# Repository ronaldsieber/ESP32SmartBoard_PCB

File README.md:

# ESP32SmartBoard_PCB
**KiCad project of a Printed Cuircit Board (PCB) for ESP32 with Temperature/Humidity/CO2 Sensors, User LEDs and Buttons.**

In the past I've implemented various Smart Projects with the ESP32 on break-out boards. On the one hand, break-out boards are very useful because they make hardware modifications as easy as software changes. On the other hand, it is very cumbersome to build several copies of the same circuit with break-out boards. Furthermore, they are mechanically fragile and not really particularly visually appealing. Therefore they are not very suitable for permanent use in the visible area of living rooms.

For this reason I designed the **ESP32SmartBoard_PCB**, which combines different projects on a single, professionally producible PCB. This allows now for reproducing multiple copies of a device without great effort and hide them in a small housing if necessary.

## Board Features

The *ESP32SmartBoard_PCB* contains the following components:
- ESP32 Development Kit
- DHT22 (combined temperature and humidity sensor)
- MH-Z19 (CO2 sensor with integrated temperature sensor)
- 9 freely usable user LEDs (LED0..LED8, arranged in one row and usable as a LED Bar)
- 3 freely usable user Buttons (KEY0, KEY1, BLE_CFG)

![\[kicad_3d_model\]](Documentation/ESP32SmartBoard_PCB.3d-model.png)

## Board Description

The *ESP32SmartBoard_PCB* is a two-layer Printed Circuit Board (PCB), assembled on one side and only uses THT components (Through Hole Technology) that are very easy to solder. It can therefore be used very easily also by students and hobbyists.

The values of all components are specified in the [Schematic](Documentation/ESP32SmartBoard_PCB.sch.pdf).

The PCB size and the positions of the mounting holes allow installation in the plastic universal housing of 135 x 95 x 45 mm (article number 523117). This polystyrene housing (EPS) can be easily processed mechanically (e.g. cut out a viewing window for the LED Bar). It is available from various providers on the Internet.

![\[ESP32SmartBoard_OpenFrame_with_Box\]](Documentation/ESP32SmartBoard_OpenFrame_with_Box.jpg)

By searching in the Internet, several PCB manufacturers can be found who are able to directly import the KiCad layout file [ESP32SmartBoard_PCB.kicad_pcb](ESP32SmartBoard_PCB/ESP32SmartBoard_PCB.kicad_pcb). The PCBs with silkscreen (assembly printing) on the top are then sent by post after a few days.

## Power Supply

There are following options for the power supply of the board:
- Via USB connection of the ESP32 Development Kit (in this case Pin15/Vin of the ESP32DevKit acts as an output and supplies the rest of the circuit)
- Supply of 5 ... 6VDC to connector J1 (in this case the rest of the board supplies the ESP32DevKit and Pin15/Vin acts as an input)

## Commissioning

With the Arduino sketch from the [ESP32SmartBoard_IoCheck](https://github.com/ronaldsieber/ESP32SmartBoard_IoCheck) repository, all components of the board can be checked for correct function after assembly. The sketch is also a good starting point for new software projects based on this board.

## Schematic Symbols, Footprints and 3D Models

Not all schematic symbols, footprints and 3D models required for *ESP32SmartBoard_PCB* are contained in the native installed KiCad library. [External_KiCad_Parts.txt](Documentation/External_KiCad_Parts.txt) lists the additional components and their download links.

## Practice Notes

- The user LEDs are arranged in one row and can be used as a LED Bar. The colors of the LEDs should be selected according to the respective application. For example, to show the CO2 level in the form of a scale, the following grouping is suitable:
  * LED0..LED2: green = excellent
  * LED3..LED5: yellow = acceptable
  * LED6..LED8: red = critical

- It seems that there are several versions of the ESP32 Development Kit and the MH-Z19 CO2 sensor with pins of different widths. In my components, the diameter of the connection pins are larger than the diameter of the soldering pads in the footprint. This prevented me from soldering the components directly onto the board. However, I was able to solve the problem by using Pin Headers (see image above). The solder connections of the Pin Headers are small enough for the solder pads and the ESP32 Development Kit and MH-Z19 CO2 sensor can be easily plugged in.

## Software Projects for the ESP32SmartBoard

 - [ESP32SmartBoard_IoCheck](https://github.com/ronaldsieber/ESP32SmartBoard_IoCheck) - Checking of all components during commissioning and starting point for new software projects based on this board.
   
 - [ESP32SmartBoard_HttpSensors](https://github.com/ronaldsieber/ESP32SmartBoard_HttpSensors) - Embedded WebServer based Arduino Sketch for ESP32SmartBoard
   
 - [ESP32SmartBoard_MqttSensors](https://github.com/ronaldsieber/ESP32SmartBoard_MqttSensors) - MQTT Client based Arduino Sketch for ESP32SmartBoard

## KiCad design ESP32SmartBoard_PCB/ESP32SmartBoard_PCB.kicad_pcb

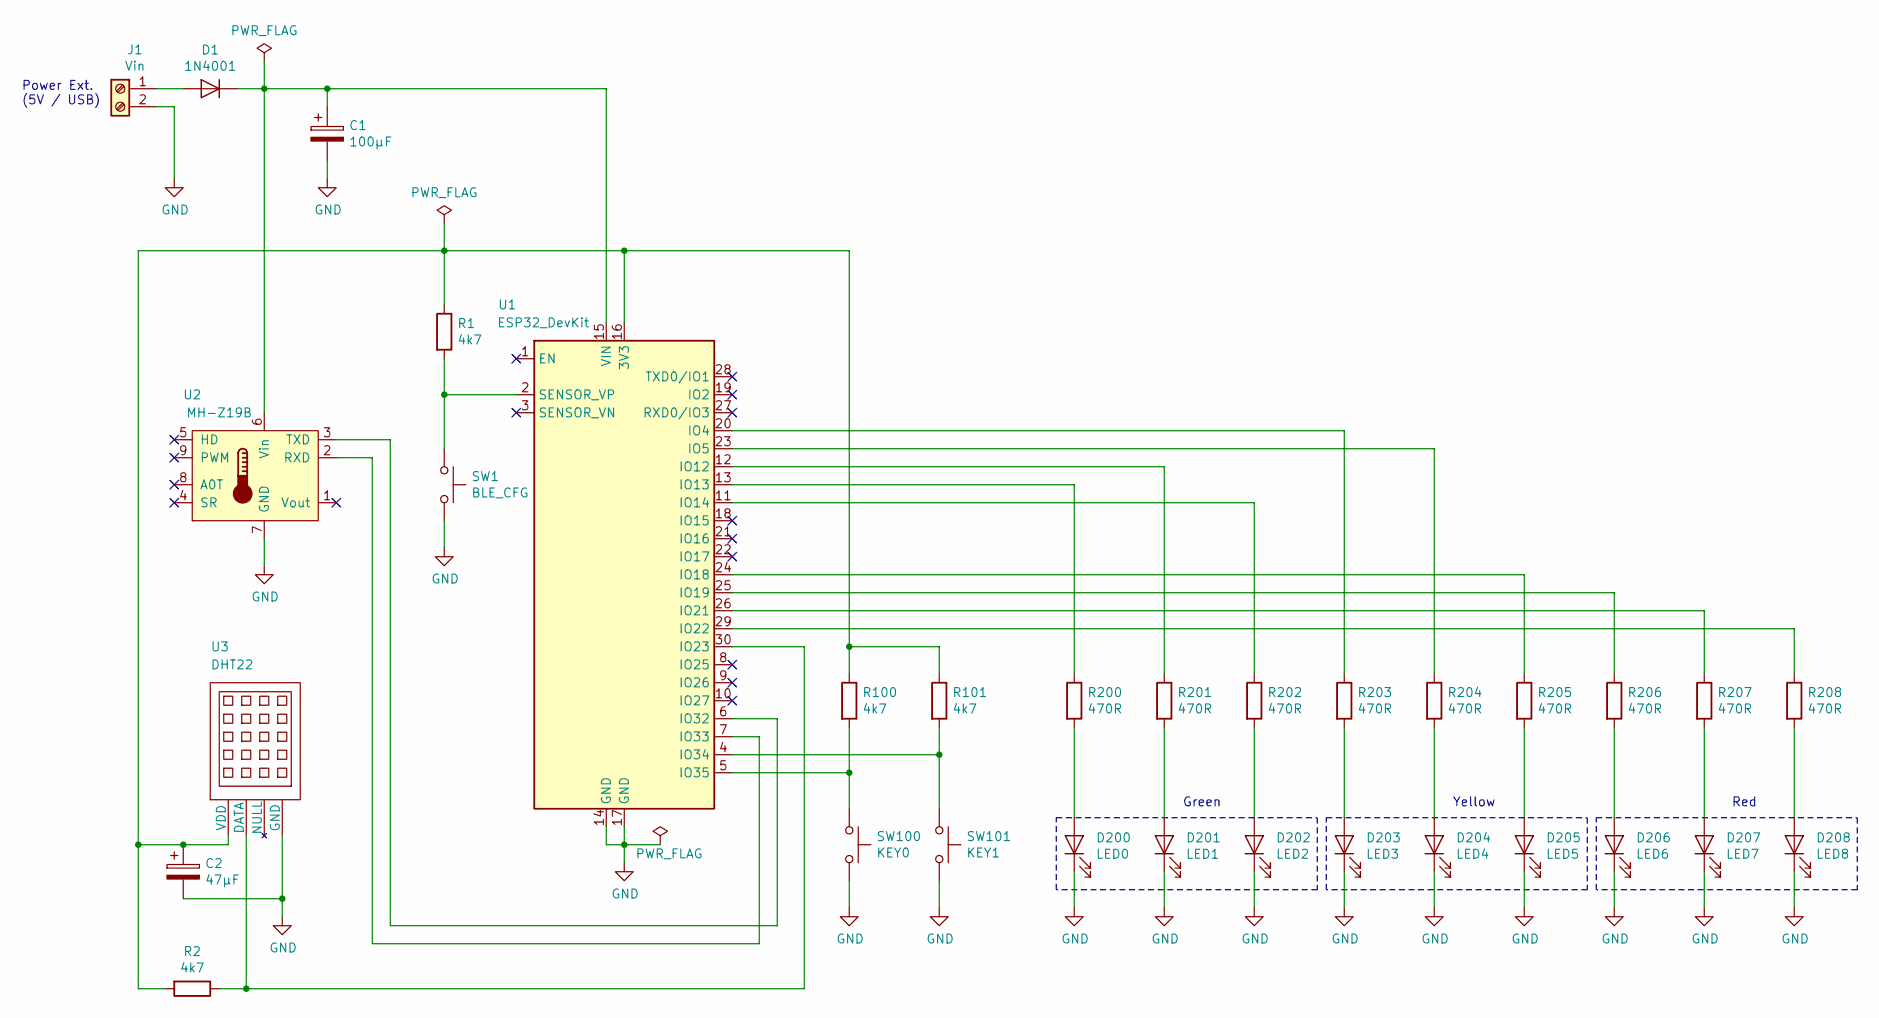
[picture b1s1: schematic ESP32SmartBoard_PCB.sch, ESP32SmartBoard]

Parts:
C1: 100µF; CP_Radial_D8.0mm_P3.50mm
C2: 47µF; CP_Radial_D8.0mm_P3.50mm
D1: 1N4001; D_5W_P12.70mm_Horizontal
D200: LED0; LED_D3.0mm
D201: LED1; LED_D3.0mm
D202: LED2; LED_D3.0mm
D203: LED3; LED_D3.0mm
D204: LED4; LED_D3.0mm
D205: LED5; LED_D3.0mm
D206: LED6; LED_D3.0mm
D207: LED7; LED_D3.0mm
D208: LED8; LED_D3.0mm
J1: Vin; TerminalBlock_Phoenix_MKDS1.5-2pol
R1, R2, R100, R101: 4k7; R_Axial_DIN0309_L9.0mm_D3.2mm_P12.70mm_Horizontal
R200, R201, R202, R203, R204, R205, R206, R207, R208: 470R; R_Axial_DIN0309_L9.0mm_D3.2mm_P12.70mm_Horizontal
SW1: BLE_CFG; SW_PUSH_6mm_h5mm
SW100: KEY0; SW_PUSH_6mm_h5mm
SW101: KEY1; SW_PUSH_6mm_h5mm
U1: ESP32_DevKit; esp32_devkit_v1_doit
U2: MH-Z19B; Winsen_MH-Z19B
U3: DHT22; DHT22_Temperature_Humidity

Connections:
GND: C1.2, C2.2, D200.1 (K), D201.1 (K), D202.1 (K), D203.1 (K), D204.1 (K), D205.1 (K), D206.1 (K), D207.1 (K), D208.1 (K), J1.2, SW1.2, SW100.2, SW101.2, U1.14 (GND), U1.17 (GND), U2.7 (GND), U3.4 (GND)
unnamed: C1.1, D1.1 (K), U1.15 (VIN), U2.6 (Vin)
unnamed: C2.1, R1.1, R2.2, R100.1, R101.1, U1.16 (3V3), U3.1 (VDD)
unnamed: D1.2 (A), J1.1
unnamed: D200.2 (A), R200.2
unnamed: D201.2 (A), R201.2
unnamed: D202.2 (A), R202.2
unnamed: D203.2 (A), R203.2
unnamed: D204.2 (A), R204.2
unnamed: D205.2 (A), R205.2
unnamed: D206.2 (A), R206.2
unnamed: D207.2 (A), R207.2
unnamed: D208.2 (A), R208.2
unnamed: R1.2, SW1.1, U1.2 (SENSOR_VP)
unnamed: R2.1, U1.30 (IO23), U3.2 (DATA)
unnamed: R100.2, SW100.1, U1.5 (IO35)
unnamed: R101.2, SW101.1, U1.4 (IO34)
unnamed: R200.1, U1.13 (IO13)
unnamed: R201.1, U1.12 (IO12)
unnamed: R202.1, U1.11 (IO14)
unnamed: R203.1, U1.20 (IO4)
unnamed: R204.1, U1.23 (IO5)
unnamed: R205.1, U1.24 (IO18)
unnamed: R206.1, U1.25 (IO19)
unnamed: R207.1, U1.26 (IO21)
unnamed: R208.1, U1.29 (IO22)
unnamed: U1.6 (IO32), U2.3 (TXD)
unnamed: U1.7 (IO33), U2.2 (RXD)

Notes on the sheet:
Power Ext. (5V / USB)
Green
Yellow
Red

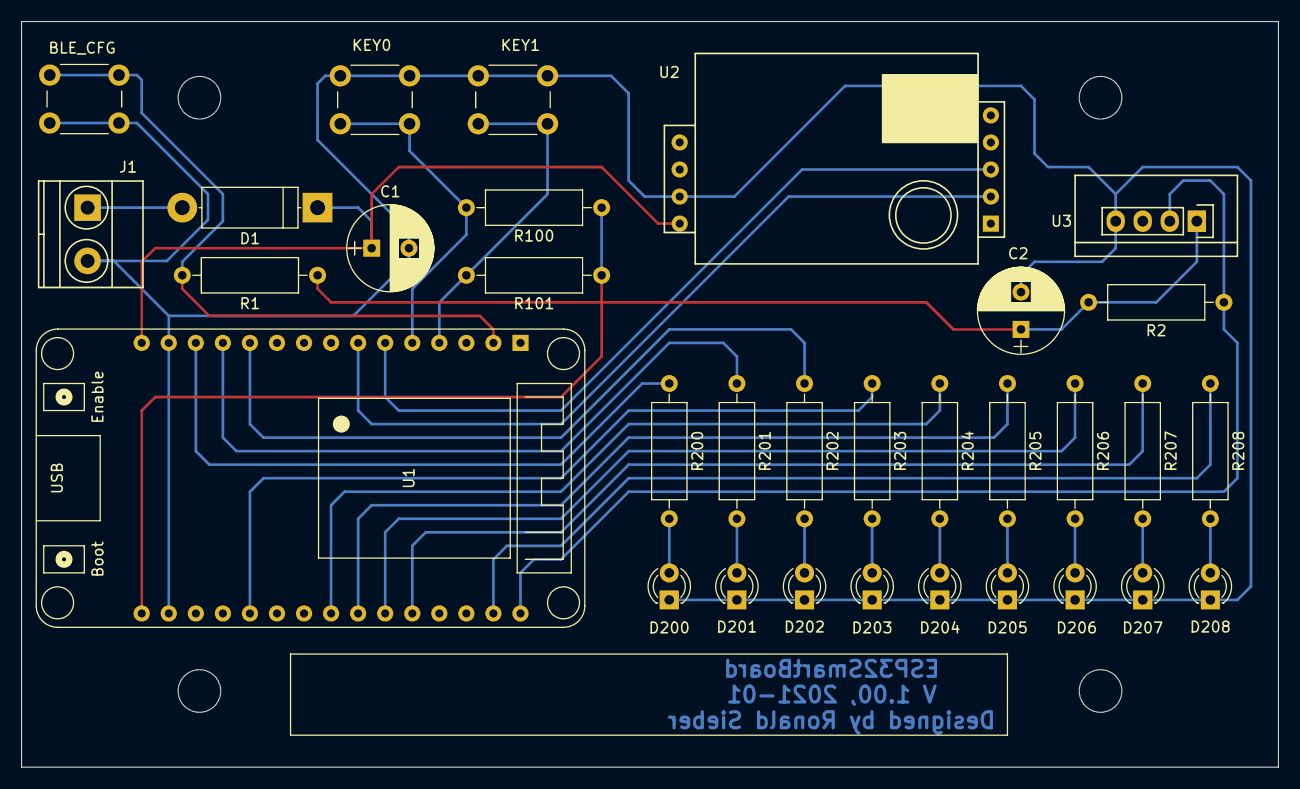
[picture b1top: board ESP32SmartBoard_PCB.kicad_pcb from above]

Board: 2 copper layers, 118.0 x 70.0 mm, 32 parts (0 on the bottom side), 28 nets.

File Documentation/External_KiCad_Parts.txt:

Part:   ESP32_DevKit_V1_DOIT
            Symbol / Footprint / 3D-Model:          https://gitlab.com/VictorLamoine/kicad

Part:   MH-Z19B
            Symbol / Footprint:                     https://gitlab.com/IT-Berater/twco2sensor-mh-z19b
            3D-Model:                               https://github.com/ronaldsieber/MH-Z19_3D_Model

Part:   DHT22
            Symbol / Footprint:                     https://github.com/skorokithakis/kicad-lib/blob/master/Senso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
            3D-Model:                               [KiCad DHT11 3D Model]

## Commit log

2021-02-01 Add files via upload
    Initial Version
2021-04-06 Update README.md
    Related software projects for the ESP32SmartBoard added
